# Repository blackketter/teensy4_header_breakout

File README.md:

A breakout board for the PJRC.com Teensy 4.0 board that is soldered directly to the bottom of the Teensy board via castellated solder points and two parallel 2x14 0.1" headers for connection.

There are companion boards that can attach to the outside pins and provide:

- [Micro SD Slot Sidecar](https://github.com/blackketter/teensy4_sd_breakout)
- [USB Host Sidecar](https://github.com/blackketter/teensy4_usb_host_breakout)
- [ESP32 WiFi & Bluetooth Sidecar](https://github.com/blackketter/teensy4_esp32_breakout)

Designed in KiCad.

Current design, avaiable at [OSHPark](https://oshpark.com/shared_projects/tZbsjC0v):

Previous prototype:

Notes:

- If you need to cut the trace between VIN and VUSB, do it before attaching board.
- You should be able to use one of [these](https://www.pjrc.com/store/cable_usb_host_t36.html) cables connected to pins 1-5 on the right side for a basic USB host connection (albeit without power management and protection). For a better protected solution see [this USB sidecar](https://github.com/blackketter/teensy4_usb_host_breakout)
- Make sure to solder all the pins marked with circles.  You may need a bit of wire to make the connection on the Teensy VUSB pin.
- When soldering the Teensy pins, make sure you give them plenty of solder, heat and time for the solder to flow to the other side.  And make sure you test the connections with a continuity tester for opens ans shorts
- A thinner PCB will make it easier to solder. (Caution: OSHPark 0.8mm thick boards are not being made reliably.  Better to use 1.6mm process.)
- Todo: Reduce size of larger internal cutout.

Left Side Pinout:

1. 34/SD DAT1
2. 35/SD DAT0
3. GND
4. 36/SD CLK
5. 3.3V
6. 37/SD CMD
7. 38/SD DAT3
8. 39/SD DAT2
9. 29
10. 31
11. 33
12. 32
13. 30
14. VBAT

Right Side Pinout:

1. VUSB
2. USB Host D-
3. USB Host D+
4. GND
5. GND
6. 27
7. 25
8. 26
9. 28
10. 24
11. 3V3
12. GND
13. Program
14. On/Off

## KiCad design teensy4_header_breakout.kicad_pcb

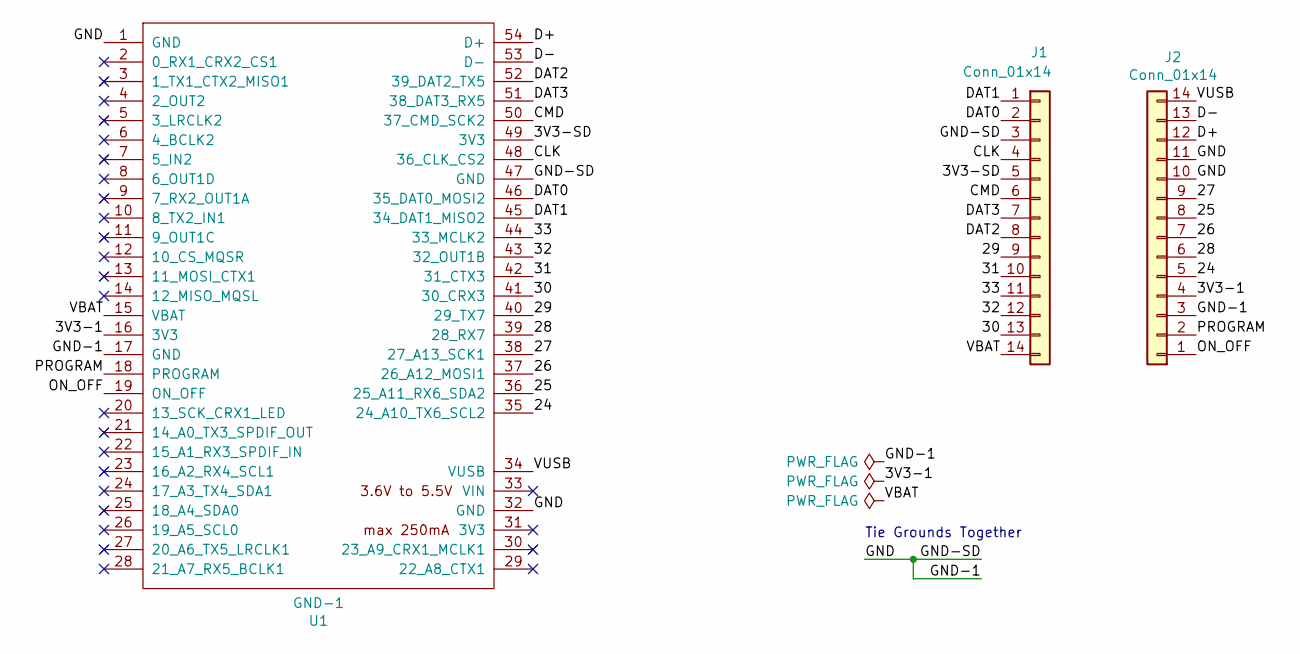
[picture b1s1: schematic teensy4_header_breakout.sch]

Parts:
J1, J2: Conn_01x14; PinHeader_1x14_P2.54mm_Vertical
U1: GND-1; Teensy40_SMT

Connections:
/3V3-1: J2.4, U1.16 (3V3)
/3V3-SD: J1.5, U1.49 (3V3)
/24: J2.5, U1.35 (24_A10_TX6_SCL2)
/25: J2.8, U1.36 (25_A11_RX6_SDA2)
/26: J2.7, U1.37 (26_A12_MOSI1)
/27: J2.9, U1.38 (27_A13_SCK1)
/28: J2.6, U1.39 (28_RX7)
/29: J1.9, U1.40 (29_TX7)
/30: J1.13, U1.41 (30_CRX3)
/31: J1.10, U1.42 (31_CTX3)
/32: J1.12, U1.43 (32_OUT1B)
/33: J1.11, U1.44 (33_MCLK2)
/CLK: J1.4, U1.48 (36_CLK_CS2)
/CMD: J1.6, U1.50 (37_CMD_SCK2)
/D+: J2.12, U1.54 (D+)
/D-: J2.13, U1.53 (D-)
/DAT0: J1.2, U1.46 (35_DAT0_MOSI2)
/DAT1: J1.1, U1.45 (34_DAT1_MISO2)
/DAT2: J1.8, U1.52 (39_DAT2_TX5)
/DAT3: J1.7, U1.51 (38_DAT3_RX5)
/GND: J1.3, J2.3, J2.10, J2.11, U1.1 (GND), U1.17 (GND), U1.32 (GND), U1.47 (GND)
/ON_OFF: J2.1, U1.19 (ON_OFF)
/PROGRAM: J2.2, U1.18 (PROGRAM)
/VBAT: J1.14, U1.15 (VBAT)
/VUSB: J2.14, U1.34 (VUSB)

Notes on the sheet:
Tie Grounds Together

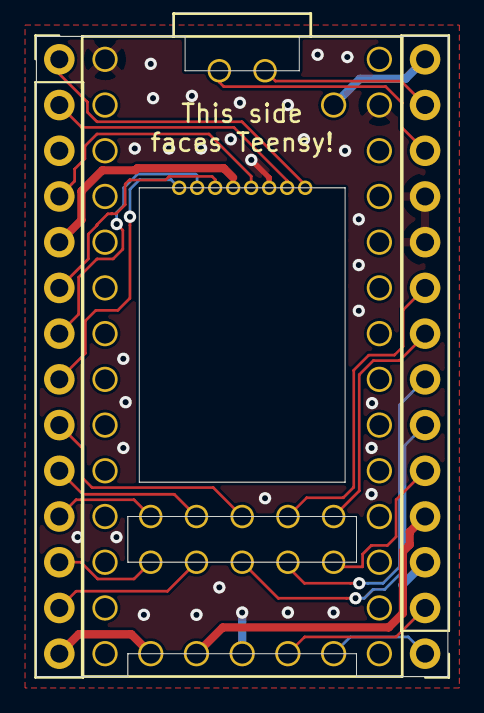
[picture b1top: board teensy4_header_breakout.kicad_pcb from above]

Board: 2 copper layers, 22.9 x 35.6 mm, 3 parts (0 on the bottom side), 25 nets.

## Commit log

2019-09-13 Add readme and rendering
2019-09-19 Photos and notes from first build
2019-09-19 Updated two unused pins to GND to allow a basic USB cable to be attached.
2019-09-19 Updated notes.
2019-09-19 Update date on silkscreen
2019-09-20 Add schematic PDF
2019-09-24 Flip Teensy on schematic to be visually closer to actual pin layout.
2019-10-04 Generated gerbers for order to AllPCB
2019-10-12 Update board with new labels and square pads
2019-10-20 Update readme, silkscreen and tweak outline
2019-10-20 Fix typo
2019-10-21 Added ground plane and graphics for sidecars
2019-10-21 Fix date
2019-10-21 Update schematic
2019-10-21 Add gnd pin to plane
2019-10-21 Add OSHPark link
2019-10-21 add pin labels to silkscreen
2019-10-21 Updated OSHPark project
2019-12-05 More ground plane, add todo
